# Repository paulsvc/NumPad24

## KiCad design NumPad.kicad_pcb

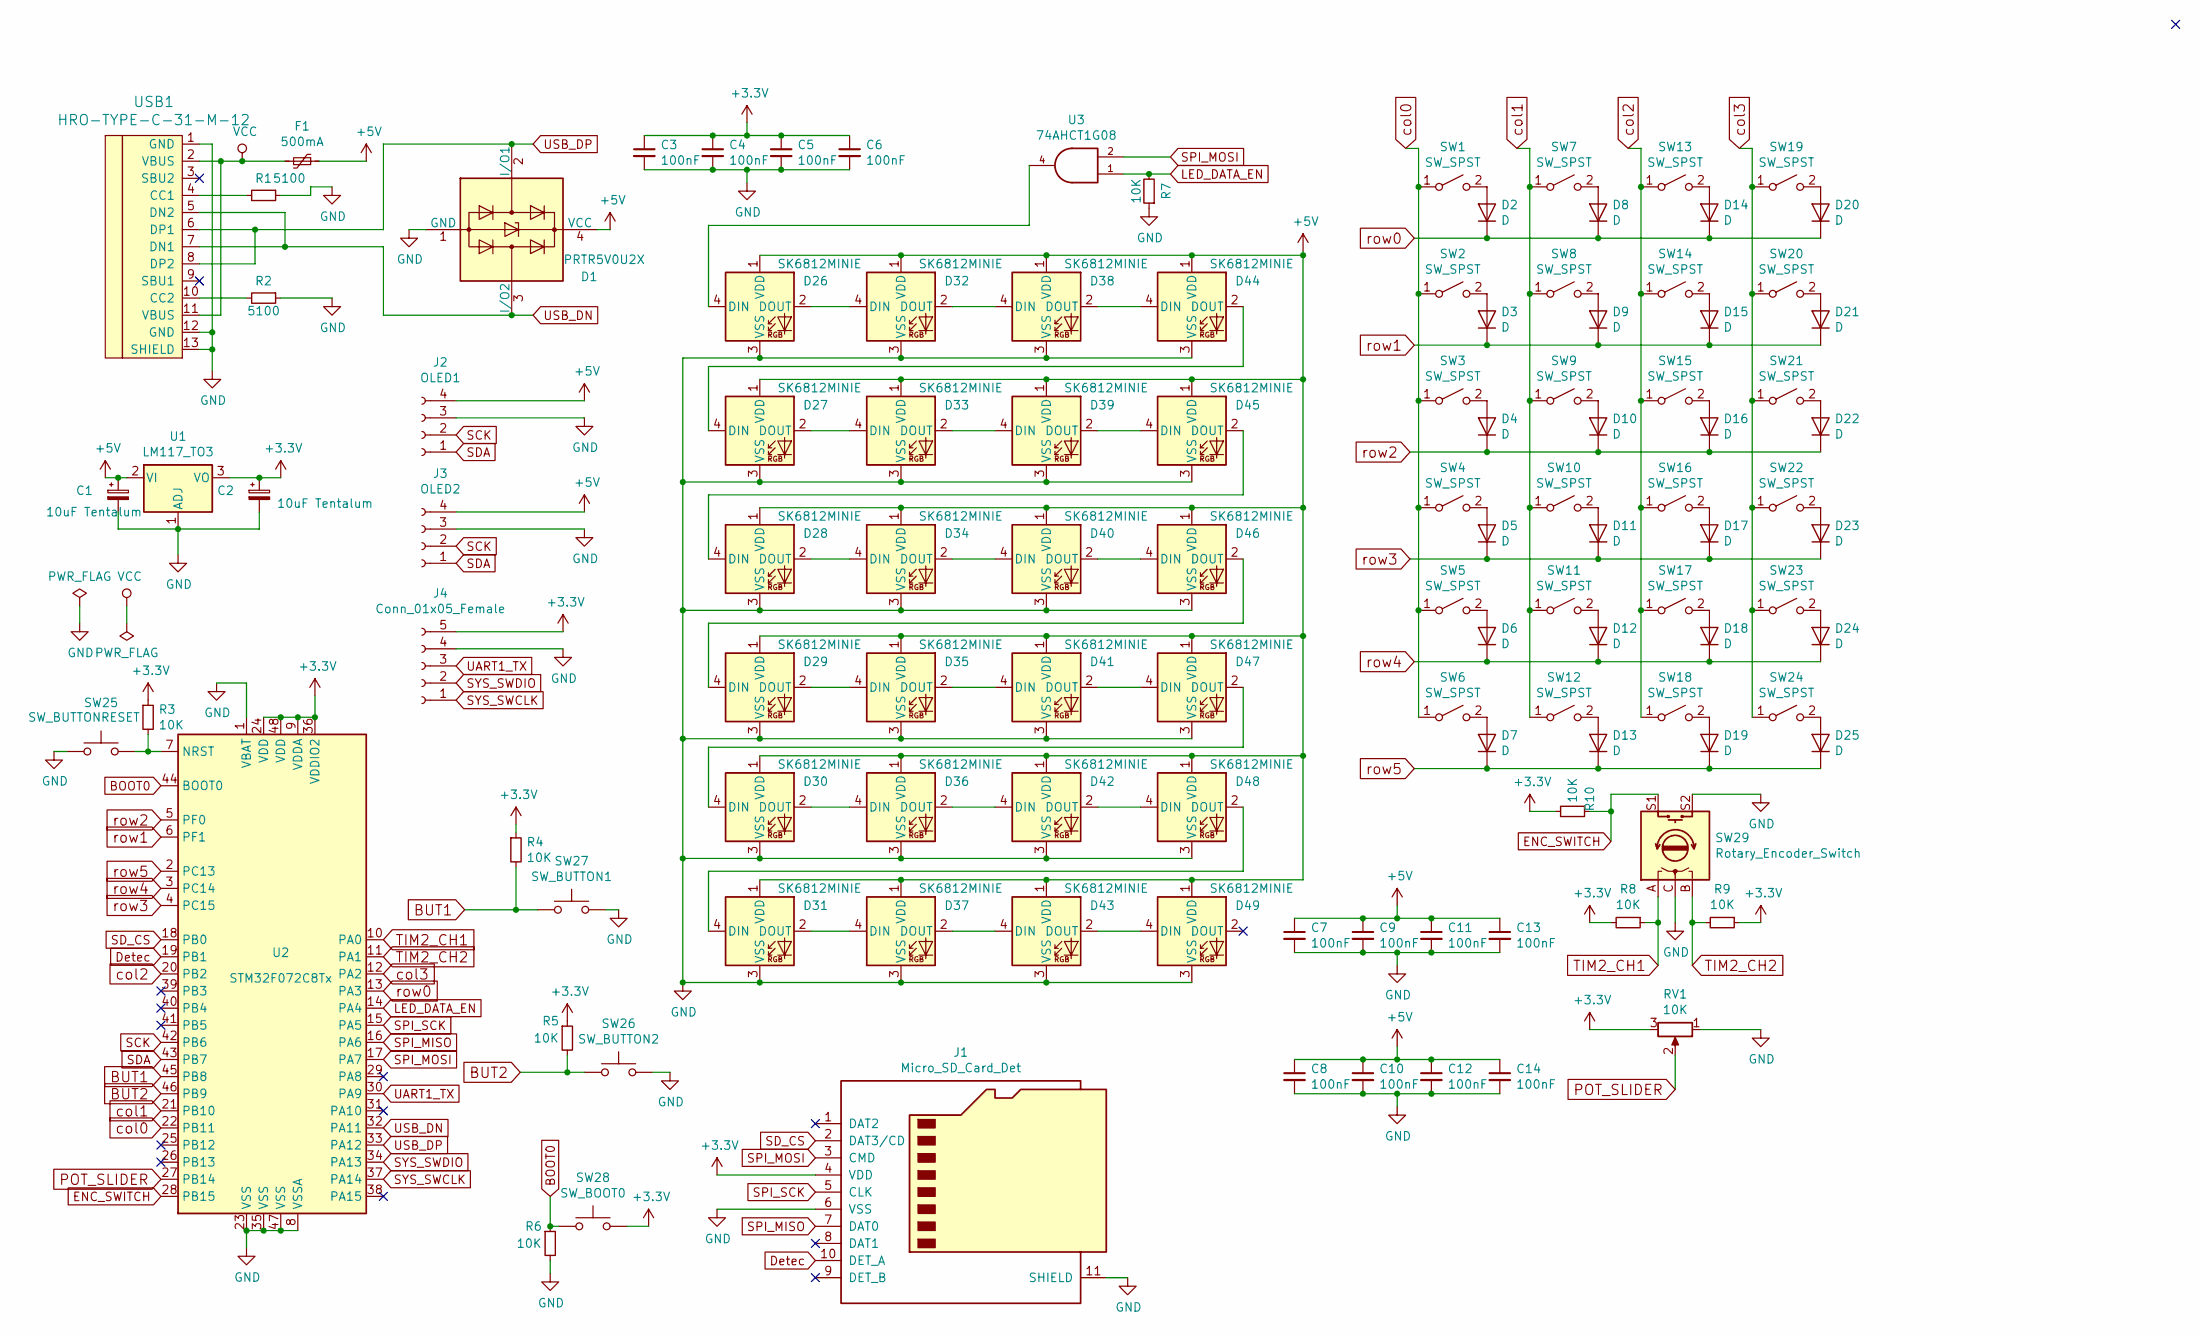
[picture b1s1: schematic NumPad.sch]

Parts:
C1, C2: 10uF Tentalum; CP_EIA-3216-18_Kemet-A_Pad1.58x1.35mm_HandSolder
C3, C4, C5, C6, C7, C8, C9, C10, C11, C12, C13, C14: 100nF; C_0603_1608Metric_Pad1.05x0.95mm_HandSolder
D1: PRTR5V0U2X; SOT143B
D2, D3, D4, D5, D6, D7, D8, D9, D10, D11, D12, D13, D14, D15, D16, D17, D18, D19, D20, D21, D22, D23, D24, D25: D; D_SOD-123
D26, D27, D28, D29, D30, D31, D32, D33, D34, D35, D36, D37, D38, D39, D40, D41, D42, D43, D44, D45, D46, D47, D48, D49: SK6812MINIE; YS-SK6812MINI-E
F1: 500mA; Fuse_1206_3216Metric_Pad1.42x1.75mm_HandSolder
J1: Micro_SD_Card_Det; microSD_HC_Molex_104031-0811
J2: OLED1; PinHeader_1x04_P2.54mm_Vertical
J3: OLED2; PinHeader_1x04_P2.54mm_Vertical
J4: Conn_01x05_Female; PinHeader_1x05_P2.54mm_Vertical
R1, R2: 5100; R_0603_1608Metric
R3, R4, R5, R6, R7, R8, R9, R10: 10K; R_0603_1608Metric
RV1: 10K; TRIM_PTA3043-2010CIA503
SW1, SW2, SW3, SW4, SW5, SW6, SW7, SW8, SW9, SW10, SW11, SW12, SW13, SW14, SW15, SW16, SW17, SW18, SW19, SW20, SW21, SW22, SW23, SW24: SW_SPST; MXOnly-1U-NoLED
SW25: SW_BUTTONRESET; SKQG-1155865
SW26: SW_BUTTON2; TactSwitch
SW27: SW_BUTTON1; TactSwitch
SW28: SW_BOOT0; SKQG-1155865
SW29: Rotary_Encoder_Switch; RotaryEncoder_Alps_EC11E-Switch_Vertical_H20mm
U1: LM117_TO3; SOT-23-5_HandSoldering
U2: STM32F072C8Tx; LQFP-48_7x7mm_P0.5mm
U3: 74AHCT1G08; SOT-23-5_HandSoldering
USB1: HRO-TYPE-C-31-M-12; HRO-TYPE-C-31-M-12-HandSoldering

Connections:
+3V3: C2.1, C3.1, C4.1, C5.1, C6.1, J1.4 (VDD), J4.5, R3.1, R4.1, R5.1, R8.2, R9.1, R10.2, RV1.3, SW28.2, U1.3 (VO), U2.9 (VDDA), U2.24 (VDD), U2.36 (VDDIO2), U2.48 (VDD)
+5V: C1.1, C7.1, C8.1, C9.1, C10.1, C11.1, C12.1, C13.1, C14.1, D1.4 (VCC), D26.1 (VDD), D27.1 (VDD), D28.1 (VDD), D29.1 (VDD), D30.1 (VDD), D31.1 (VDD), D32.1 (VDD), D33.1 (VDD), D34.1 (VDD), D35.1 (VDD), D36.1 (VDD), D37.1 (VDD), D38.1 (VDD), D39.1 (VDD), D40.1 (VDD), D41.1 (VDD), D42.1 (VDD), D43.1 (VDD), D44.1 (VDD), D45.1 (VDD), D46.1 (VDD), D47.1 (VDD), D48.1 (VDD), D49.1 (VDD), F1.1, J2.4, J3.4, U1.2 (VI), U3.5 (VCC)
BOOT0: R6.1, SW28.1, U2.44 (BOOT0)
BUT1: R4.2, SW27.1, U2.45 (PB8)
BUT2: R5.2, SW26.1, U2.46 (PB9)
Detec: J1.10 (DET_A), U2.19 (PB1)
ENC_SWITCH: R10.1, SW29.S1, U2.28 (PB15)
GND: C1.2, C2.2, C3.2, C4.2, C5.2, C6.2, C7.2, C8.2, C9.2, C10.2, C11.2, C12.2, C13.2, C14.2, D1.1 (GND), D26.3 (VSS), D27.3 (VSS), D28.3 (VSS), D29.3 (VSS), D30.3 (VSS), D31.3 (VSS), D32.3 (VSS), D33.3 (VSS), D34.3 (VSS), D35.3 (VSS), D36.3 (VSS), D37.3 (VSS), D38.3 (VSS), D39.3 (VSS), D40.3 (VSS), D41.3 (VSS), D42.3 (VSS), D43.3 (VSS), D44.3 (VSS), D45.3 (VSS), D46.3 (VSS), D47.3 (VSS), D48.3 (VSS), D49.3 (VSS), J1.6 (VSS), J1.11 (SHIELD), J2.3, J3.3, J4.4, R1.1, R2.1, R6.2, R7.1, RV1.1, SW25.1, SW26.2, SW27.2, SW29.C, SW29.S2, U1.1 (ADJ), U2.1 (VBAT), U2.8 (VSSA), U2.23 (VSS), U2.35 (VSS), U2.47 (VSS), U3.3 (GND), USB1.1 (GND), USB1.12 (GND), USB1.13 (SHIELD)
LED_DATA_EN: R7.2, U2.14 (PA4), U3.1
unnamed: D2.2 (A), SW1.2 (B)
unnamed: D3.2 (A), SW2.2 (B)
unnamed: D4.2 (A), SW3.2 (B)
unnamed: D5.2 (A), SW4.2 (B)
unnamed: D6.2 (A), SW5.2 (B)
unnamed: D7.2 (A), SW6.2 (B)
unnamed: D8.2 (A), SW7.2 (B)
unnamed: D9.2 (A), SW8.2 (B)
unnamed: D10.2 (A), SW9.2 (B)
unnamed: D11.2 (A), SW10.2 (B)
unnamed: D12.2 (A), SW11.2 (B)
unnamed: D13.2 (A), SW12.2 (B)
unnamed: D14.2 (A), SW13.2 (B)
unnamed: D15.2 (A), SW14.2 (B)
unnamed: D16.2 (A), SW15.2 (B)
unnamed: D17.2 (A), SW16.2 (B)
unnamed: D18.2 (A), SW17.2 (B)
unnamed: D19.2 (A), SW18.2 (B)
unnamed: D20.2 (A), SW19.2 (B)
unnamed: D21.2 (A), SW20.2 (B)
unnamed: D22.2 (A), SW21.2 (B)
unnamed: D23.2 (A), SW22.2 (B)
unnamed: D24.2 (A), SW23.2 (B)
unnamed: D25.2 (A), SW24.2 (B)
unnamed: D26.2 (DOUT), D32.4 (DIN)
unnamed: D26.4 (DIN), U3.4
unnamed: D27.2 (DOUT), D33.4 (DIN)
unnamed: D27.4 (DIN), D44.2 (DOUT)
unnamed: D28.2 (DOUT), D34.4 (DIN)
unnamed: D28.4 (DIN), D45.2 (DOUT)
unnamed: D29.2 (DOUT), D35.4 (DIN)
unnamed: D29.4 (DIN), D46.2 (DOUT)
unnamed: D30.2 (DOUT), D36.4 (DIN)
unnamed: D30.4 (DIN), D47.2 (DOUT)
unnamed: D31.2 (DOUT), D37.4 (DIN)
unnamed: D31.4 (DIN), D48.2 (DOUT)
unnamed: D32.2 (DOUT), D38.4 (DIN)
unnamed: D33.2 (DOUT), D39.4 (DIN)
unnamed: D34.2 (DOUT), D40.4 (DIN)
unnamed: D35.2 (DOUT), D41.4 (DIN)
unnamed: D36.2 (DOUT), D42.4 (DIN)
unnamed: D37.2 (DOUT), D43.4 (DIN)
unnamed: D38.2 (DOUT), D44.4 (DIN)
unnamed: D39.2 (DOUT), D45.4 (DIN)
unnamed: D40.2 (DOUT), D46.4 (DIN)
unnamed: D41.2 (DOUT), D47.4 (DIN)
unnamed: D42.2 (DOUT), D48.4 (DIN)
unnamed: D43.2 (DOUT), D49.4 (DIN)
unnamed: R1.2, USB1.4 (CC1)
unnamed: R2.2, USB1.10 (CC2)
unnamed: R3.2, SW25.2, U2.7 (NRST)
POT_SLIDER: RV1.2, U2.27 (PB14)
SCK: J2.2, J3.2, U2.42 (PB6)
SDA: J2.1, J3.1, U2.43 (PB7)
SD_CS: J1.2 (DAT3/CD), U2.18 (PB0)
SPI_MISO: J1.7 (DAT0), U2.16 (PA6)
SPI_MOSI: J1.3 (CMD), U2.17 (PA7), U3.2
SPI_SCK: J1.5 (CLK), U2.15 (PA5)
SYS_SWCLK: J4.1, U2.37 (PA14)
SYS_SWDIO: J4.2, U2.34 (PA13)
TIM2_CH1: R8.1, SW29.A, U2.10 (PA0)
TIM2_CH2: R9.2, SW29.B, U2.11 (PA1)
UART1_TX: J4.3, U2.30 (PA9)
USB_DN: D1.3 (I/O2), U2.32 (PA11), USB1.5 (DN2), USB1.7 (DN1)
USB_DP: D1.2 (I/O1), U2.33 (PA12), USB1.6 (DP1), USB1.8 (DP2)
VCC: F1.2, USB1.2 (VBUS), USB1.11 (VBUS)
col0: SW1.1 (A), SW2.1 (A), SW3.1 (A), SW4.1 (A), SW5.1 (A), SW6.1 (A), U2.22 (PB11)
col1: SW7.1 (A), SW8.1 (A), SW9.1 (A), SW10.1 (A), SW11.1 (A), SW12.1 (A), U2.21 (PB10)
col2: SW13.1 (A), SW14.1 (A), SW15.1 (A), SW16.1 (A), SW17.1 (A), SW18.1 (A), U2.20 (PB2)
col3: SW19.1 (A), SW20.1 (A), SW21.1 (A), SW22.1 (A), SW23.1 (A), SW24.1 (A), U2.12 (PA2)
row0: D2.1 (K), D8.1 (K), D14.1 (K), D20.1 (K), U2.13 (PA3)
row1: D3.1 (K), D9.1 (K), D15.1 (K), D21.1 (K), U2.6 (PF1)
row2: D4.1 (K), D10.1 (K), D16.1 (K), D22.1 (K), U2.5 (PF0)
row3: D5.1 (K), D11.1 (K), D17.1 (K), D23.1 (K), U2.4 (PC15)
row4: D6.1 (K), D12.1 (K), D18.1 (K), D24.1 (K), U2.3 (PC14)
row5: D7.1 (K), D13.1 (K), D19.1 (K), D25.1 (K), U2.2 (PC13)

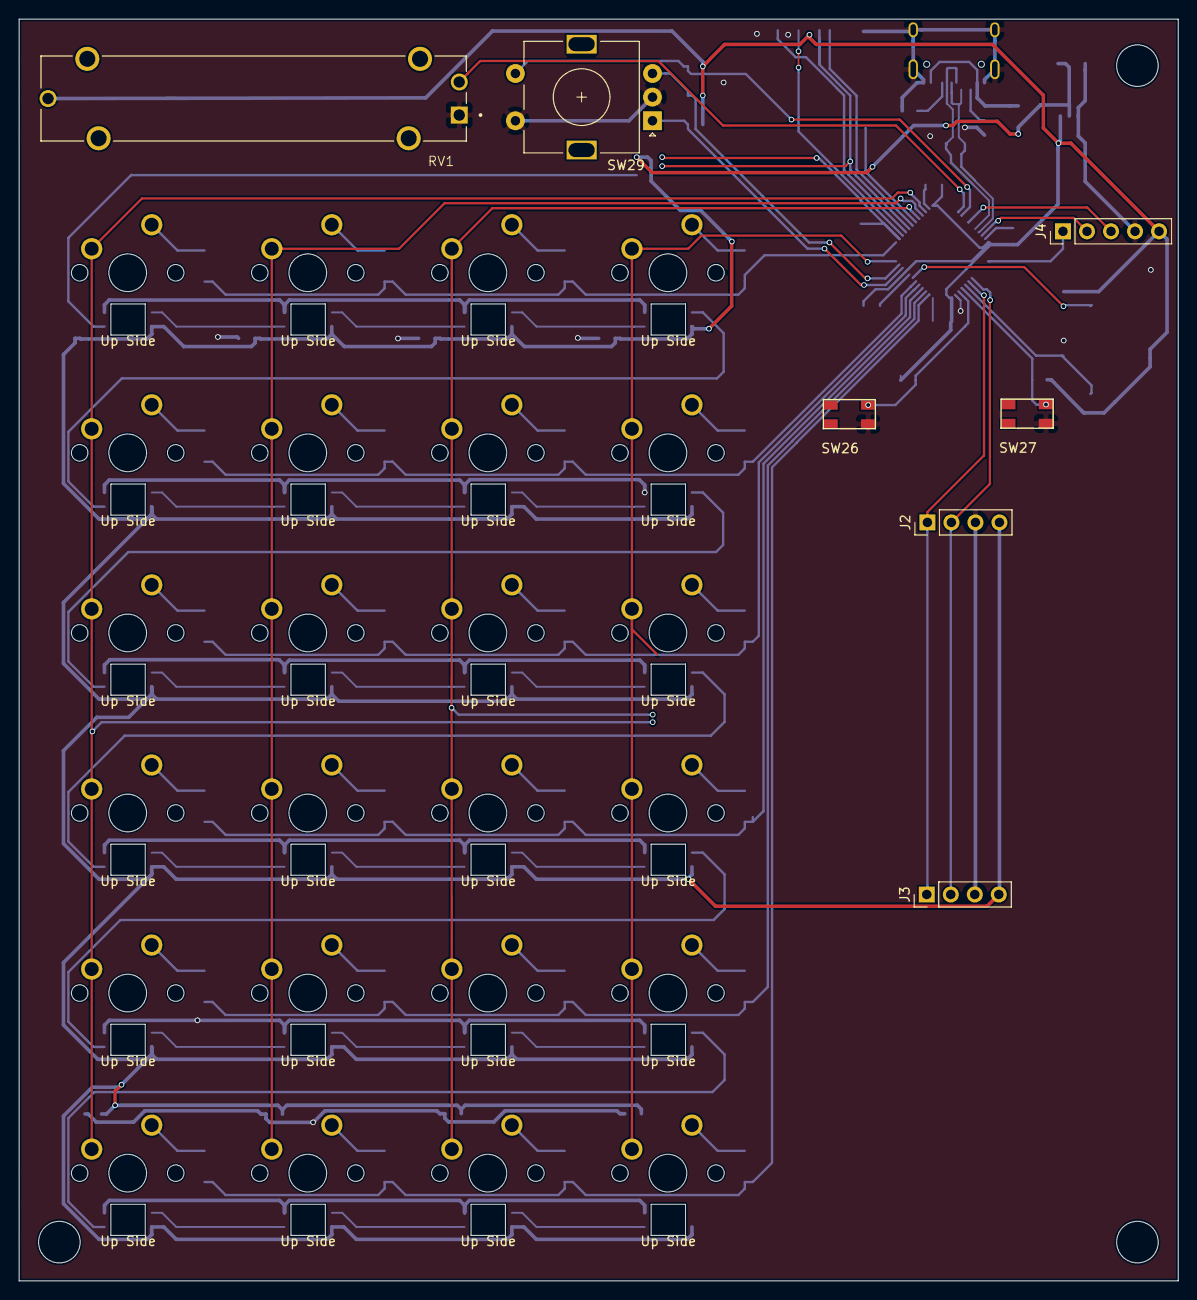
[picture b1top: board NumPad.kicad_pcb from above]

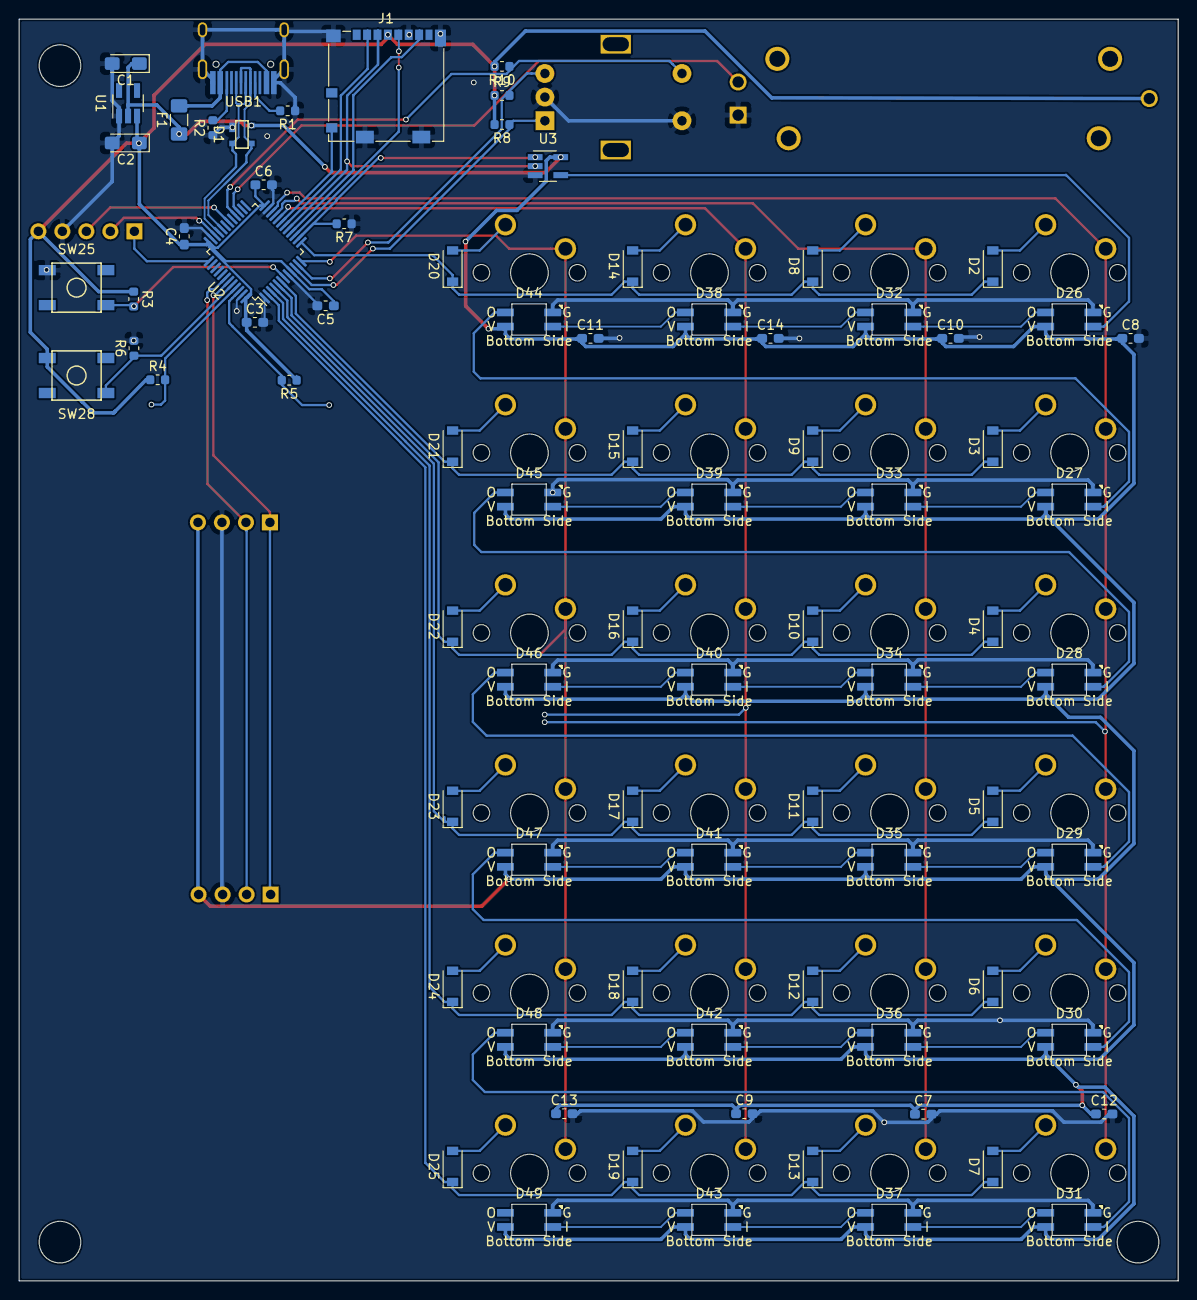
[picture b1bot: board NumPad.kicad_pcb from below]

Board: 2 copper layers, 122.6 x 133.5 mm, 112 parts (81 on the bottom side), 85 nets.

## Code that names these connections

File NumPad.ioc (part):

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Mcu.Name=STM32F072C(8-B)Tx
Mcu.Package=LQFP48
Mcu.UserName=STM32F072C8Tx
PA0.GPIOParameters=GPIO_ModeDefaultPP,GPIO_Speed,GPIO_PuPd
PA0.GPIO_ModeDefaultPP=GPIO_MODE_AF_OD
PA0.GPIO_PuPd=GPIO_PULLUP
PA0.GPIO_Speed=GPIO_SPEED_FREQ_HIGH
PA0.Signal=S_TIM2_CH1_ETR
PA1.GPIOParameters=GPIO_ModeDefaultPP,GPIO_Speed,GPIO_PuPd
PA1.GPIO_ModeDefaultPP=GPIO_MODE_AF_OD
PA1.GPIO_PuPd=GPIO_PULLUP
PA1.GPIO_Speed=GPIO_SPEED_FREQ_HIGH
PA1.Signal=S_TIM2_CH2
PA11.Mode=Device
PA11.Signal=USB_DM
PA12.Mode=Device
PA12.Signal=USB_DP
PA13.Mode=Serial_Wire
PA13.Signal=SYS_SWDIO
PA14.Mode=Serial_Wire
PA14.Signal=SYS_SWCLK
PA2.GPIOParameters=GPIO_Label
PA2.GPIO_Label=col3
PA2.Signal=GPIO_Output
PA3.GPIOParameters=GPIO_PuPd,GPIO_Label
PA3.GPIO_Label=row0
PA3.GPIO_PuPd=GPIO_PULLUP
PA3.Signal=GPIO_Input
PA4.GPIOParameters=GPIO_Label
PA4.GPIO_Label=LED_DATA_EN
PA4.Signal=GPIO_Output
PA5.Mode=Full_Duplex_Master
PA5.Signal=SPI1_SCK
PA6.Mode=Full_Duplex_Master
PA6.Signal=SPI1_MISO
PA7.Mode=Full_Duplex_Master
PA7.Signal=SPI1_MOSI
PA9.Mode=Half_duplex(single_wire_mode)
PA9.Signal=USART1_TX
PB0.GPIOParameters=PinState,GPIO_PuPd,GPIO_Label
PB0.GPIO_Label=SD_CS
PB0.GPIO_PuPd=GPIO_NOPULL
PB0.PinState=GPIO_PIN_SET
PB0.Signal=GPIO_Output
PB1.GPIOParameters=GPIO_Label
PB1.GPIO_Label=CARD_DETECT
PB1.Signal=GPXTI1
PB10.GPIOParameters=GPIO_Label
PB10.GPIO_Label=col1
PB10.Signal=GPIO_Output
PB11.GPIOParameters=GPIO_Label
PB11.GPIO_Label=col0
PB11.Signal=GPIO_Output
PB14.GPIOParameters=GPIO_Label
PB14.GPIO_Label=POT_SLIDER
PB14.Signal=GPIO_Analog
PB15.GPIOParameters=GPIO_Label
PB15.GPIO_Label=ENC_SWITCH
PB15.Signal=GPIO_Input
PB2.GPIOParameters=GPIO_Label
PB2.GPIO_Label=col2
PB2.Signal=GPIO_Output
PB6.Mode=I2C
PB6.Signal=I2C1_SCL
PB7.Mode=I2C
PB7.Signal=I2C1_SDA
PB8.GPIOParameters=GPIO_PuPd,GPIO_Label
PB8.GPIO_Label=BUTTON_1
PB8.GPIO_PuPd=GPIO_PULLUP
PB8.Signal=GPIO_Input
PB9.GPIOParameters=GPIO_PuPd,GPIO_Label
PB9.GPIO_Label=BUTTON_2
PB9.GPIO_PuPd=GPIO_PULLUP
PB9.Signal=GPIO_Input
PC13.GPIOParameters=GPIO_PuPd,GPIO_Label
PC13.GPIO_Label=row5
PC13.GPIO_PuPd=GPIO_PULLUP
PC13.Signal=GPIO_Input
PC14-OSC32_IN.GPIOParameters=GPIO_PuPd,GPIO_Label
PC14-OSC32_IN.GPIO_Label=row4
PC14-OSC32_IN.GPIO_PuPd=GPIO_PULLUP
PC14-OSC32_IN.Signal=GPIO_Input
PC15-OSC32_OUT.GPIOParameters=GPIO_PuPd,GPIO_Label
PC15-OSC32_OUT.GPIO_Label=row3
PC15-OSC32_OUT.GPIO_PuPd=GPIO_PULLUP
PC15-OSC32_OUT.Signal=GPIO_Input
PF0-OSC_IN.GPIOParameters=GPIO_PuPd,GPIO_Label
PF0-OSC_IN.GPIO_Label=row2
PF0-OSC_IN.GPIO_PuPd=GPIO_PULLUP
PF0-OSC_IN.Signal=GPIO_Input
PF1-OSC_OUT.GPIOParameters=GPIO_PuPd,GPIO_Label
PF1-OSC_OUT.GPIO_Label=row1
PF1-OSC_OUT.GPIO_PuPd=GPIO_PULLUP
PF1-OSC_OUT.Signal=GPIO_Input
RCC.SYSCLKFreq_VALUE=40000000
RCC.SYSCLKSource=RCC_SYSCLKSOURCE_PLLCLK
board=lul

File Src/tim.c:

/**
  ******************************************************************************
  * File Name          : TIM.c
  * Description        : This file provides code for the configuration
  *                      of the TIM instances.
  ******************************************************************************
  * @attention
  *
  * <h2><center>&copy; Copyright (c) 2020 STMicroelectronics.
  * All rights reserved.</center></h2>
  *
  * This software component is licensed by ST under Ultimate Liberty license
  * SLA0044, the "License"; You may not use this file except in compliance with
  * the License. You may obtain a copy of the License at:
  *                             www.st.com/SLA0044
  *
  ******************************************************************************
  */

/* Includes ------------------------------------------------------------------*/
#include "tim.h"

/* USER CODE BEGIN 0 */

/* USER CODE END 0 */

TIM_HandleTypeDef htim2;

/* TIM2 init function */
void MX_TIM2_Init(void)
{
  TIM_Encoder_InitTypeDef sConfig = {0};
  TIM_MasterConfigTypeDef sMasterConfig = {0};

  htim2.Instance = TIM2;
  htim2.Init.Prescaler = 0;
  htim2.Init.CounterMode = TIM_COUNTERMODE_UP;
  htim2.Init.Period = 0;
  htim2.Init.ClockDivision = TIM_CLOCKDIVISION_DIV1;
  htim2.Init.AutoReloadPreload = TIM_AUTORELOAD_PRELOAD_DISABLE;
  sConfig.EncoderMode = TIM_ENCODERMODE_TI1;
  sConfig.IC1Polarity = TIM_ICPOLARITY_RISING;
  sConfig.IC1Selection = TIM_ICSELECTION_DIRECTTI;
  sConfig.IC1Prescaler = TIM_ICPSC_DIV1;
  sConfig.IC1Filter = 0;
  sConfig.IC2Polarity = TIM_ICPOLARITY_RISING;
  sConfig.IC2Selection = TIM_ICSELECTION_DIRECTTI;
  sConfig.IC2Prescaler = TIM_ICPSC_DIV1;
  sConfig.IC2Filter = 0;
  if (HAL_TIM_Encoder_Init(&htim2, &sConfig) != HAL_OK)
  {
    Error_Handler();
  }
  sMasterConfig.MasterOutputTrigger = TIM_TRGO_RESET;
  sMasterConfig.MasterSlaveMode = TIM_MASTERSLAVEMODE_DISABLE;
  if (HAL_TIMEx_MasterConfigSynchronization(&htim2, &sMasterConfig) != HAL_OK)
  {
    Error_Handler();
  }

}

void HAL_TIM_Encoder_MspInit(TIM_HandleTypeDef* tim_encoderHandle)
{

  GPIO_InitTypeDef GPIO_InitStruct = {0};
  if(tim_encoderHandle->Instance==TIM2)
  {
  /* USER CODE BEGIN TIM2_MspInit 0 */

  /* USER CODE END TIM2_MspInit 0 */
    /* TIM2 clock enable */
    __HAL_RCC_TIM2_CLK_ENABLE();
  
    __HAL_RCC_GPIOA_CLK_ENABLE();
    /**TIM2 GPIO Configuration    
    PA0     ------> TIM2_CH1
    PA1     ------> TIM2_CH2 
    */
    GPIO_InitStruct.Pin = GPIO_PIN_0|GPIO_PIN_1;
    GPIO_InitStruct.Mode = GPIO_MODE_AF_OD;
    GPIO_InitStruct.Pull = GPIO_PULLUP;
    GPIO_InitStruct.Speed = GPIO_SPEED_FREQ_HIGH;
    GPIO_InitStruct.Alternate = GPIO_AF2_TIM2;
    HAL_GPIO_Init(GPIOA, &GPIO_InitStruct);

  /* USER CODE BEGIN TIM2_MspInit 1 */

  /* USER CODE END TIM2_MspInit 1 */
  }
}

void HAL_TIM_Encoder_MspDeInit(TIM_HandleTypeDef* tim_encoderHandle)
{

  if(tim_encoderHandle->Instance==TIM2)
  {
  /* USER CODE BEGIN TIM2_MspDeInit 0 */

  /* USER CODE END TIM2_MspDeInit 0 */
    /* Peripheral clock disable */
    __HAL_RCC_TIM2_CLK_DISABLE();
  
    /**TIM2 GPIO Configuration    
    PA0     ------> TIM2_CH1
    PA1     ------> TIM2_CH2 
    */
    HAL_GPIO_DeInit(GPIOA, GPIO_PIN_0|GPIO_PIN_1);

  /* USER CODE BEGIN TIM2_MspDeInit 1 */

  /* USER CODE END TIM2_MspDeInit 1 */
  }
} 

/* USER CODE BEGIN 1 */

/* USER CODE END 1 */

/************************ (C) COPYRIGHT STMicroelectronics *****END OF FILE****/

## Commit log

2020-04-02 Update
    Update before removing matrice
2020-04-04 Update footprints
2020-04-04 PCB Update
2020-04-04 Add footprints libs
2020-04-04 Update NumPad.kicad_pcb-bak
2020-04-04 Update PCB
